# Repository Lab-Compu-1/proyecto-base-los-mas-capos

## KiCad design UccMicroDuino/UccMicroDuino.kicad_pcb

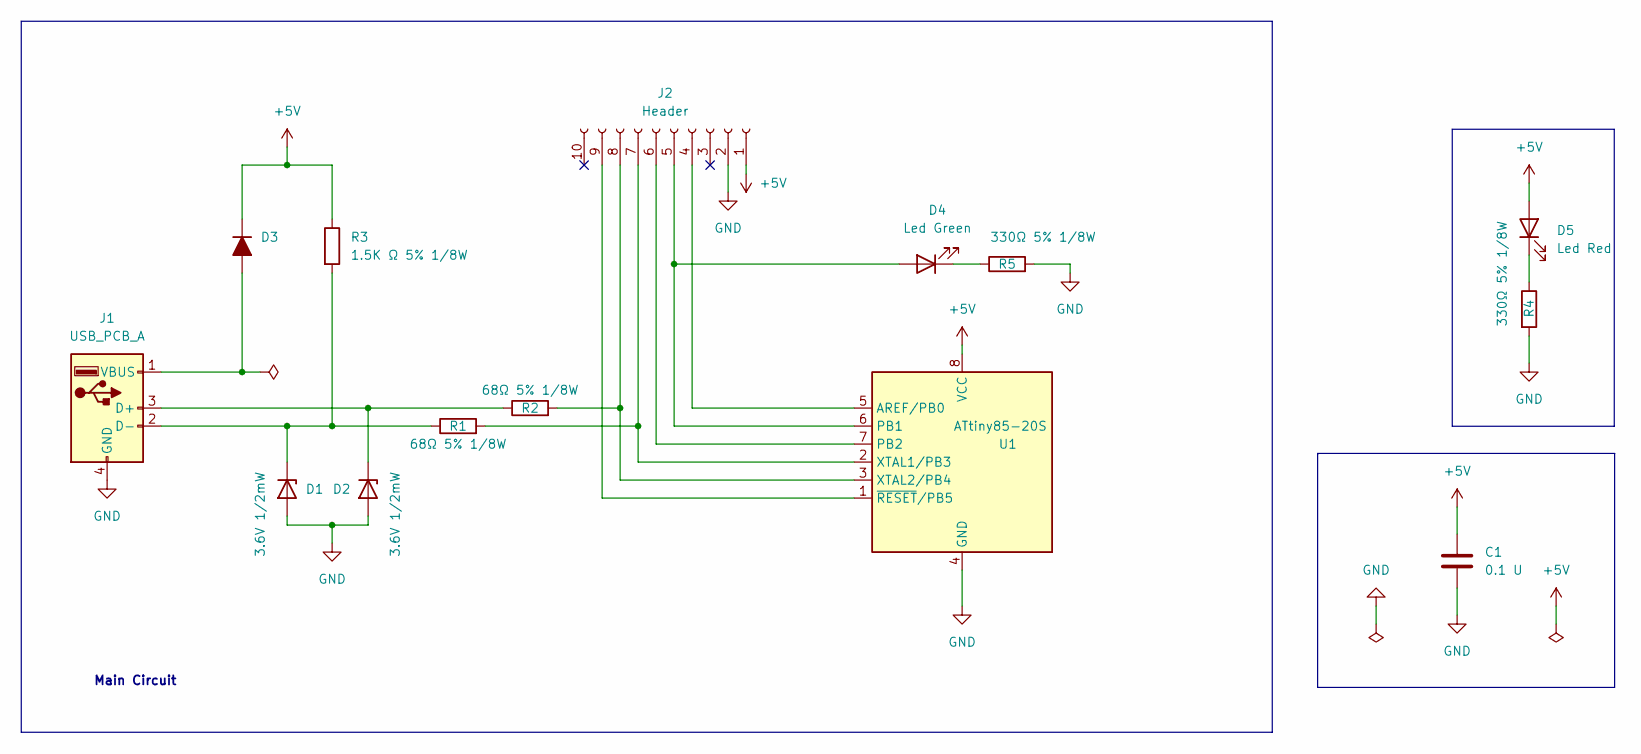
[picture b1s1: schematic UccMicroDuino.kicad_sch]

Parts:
C1: 0.1 U; C_0805_2012Metric_Pad1.18x1.45mm_HandSolder
D1, D2: 3.6V 1/2mW; D_SOD-123
D3: D_Filled; D_MiniMELF
D4: Led Green; ledSMD
D5: Led Red; ledSMD
J1: USB_PCB_A; USB_A_UCC
J2: Header; PinHeader_1x10_P2.54mm_Vertical
R1, R2: 68Ω 5% 1/8W; R_0805_2012Metric_Pad1.20x1.40mm_HandSolder
R3: 1.5K Ω 5% 1/8W; R_0805_2012Metric_Pad1.20x1.40mm_HandSolder
R4, R5: 330Ω 5% 1/8W; R_0805_2012Metric_Pad1.20x1.40mm_HandSolder
U1: ATtiny85-20S; SOIC-8_5.275x5.275mm_P1.27mm

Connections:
+5V: C1.1, D3.1 (K), D5.2 (A), J2.1, R3.1, U1.8 (VCC)
GND: C1.2, D1.2 (A), D2.2 (A), J1.4 (GND), J2.2, R4.2, R5.2, U1.4 (GND)
unnamed: D1.1 (K), J1.2 (D-), R1.1, R3.2
unnamed: D2.1 (K), J1.3 (D+), R2.1
unnamed: D3.2 (A), J1.1 (VBUS)
unnamed: D4.2 (A), J2.5, U1.6 (PB1)
unnamed: D4.1 (K), R5.1
unnamed: D5.1 (K), R4.1
unnamed: J2.4, U1.5 (AREF/PB0)
unnamed: J2.6, U1.7 (PB2)
unnamed: J2.7, R1.2, U1.2 (XTAL1/PB3)
unnamed: J2.8, R2.2, U1.3 (XTAL2/PB4)
unnamed: J2.9, U1.1 (~RESET/PB5)

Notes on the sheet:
Main Circuit

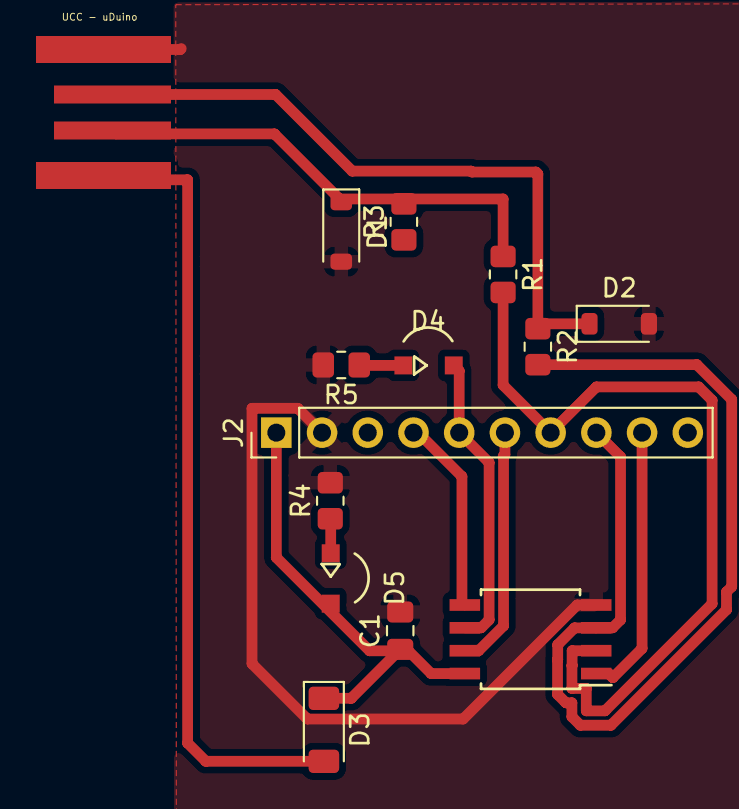
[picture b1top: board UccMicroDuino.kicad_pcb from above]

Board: 2 copper layers, 14 parts (0 on the bottom side), 13 nets.

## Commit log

2026-03-30 GitHub Classroom Feedback
2026-03-30 Setting up GitHub Classroom Feedback
2026-04-20 cambios de archivos
2026-05-18 PCB finalizado
2026-05-18 18-05-2026
2026-05-18 Arreglando la placa
2026-05-19 Placa terminada
2026-05-19 Carpeta con la pcb actualizada
